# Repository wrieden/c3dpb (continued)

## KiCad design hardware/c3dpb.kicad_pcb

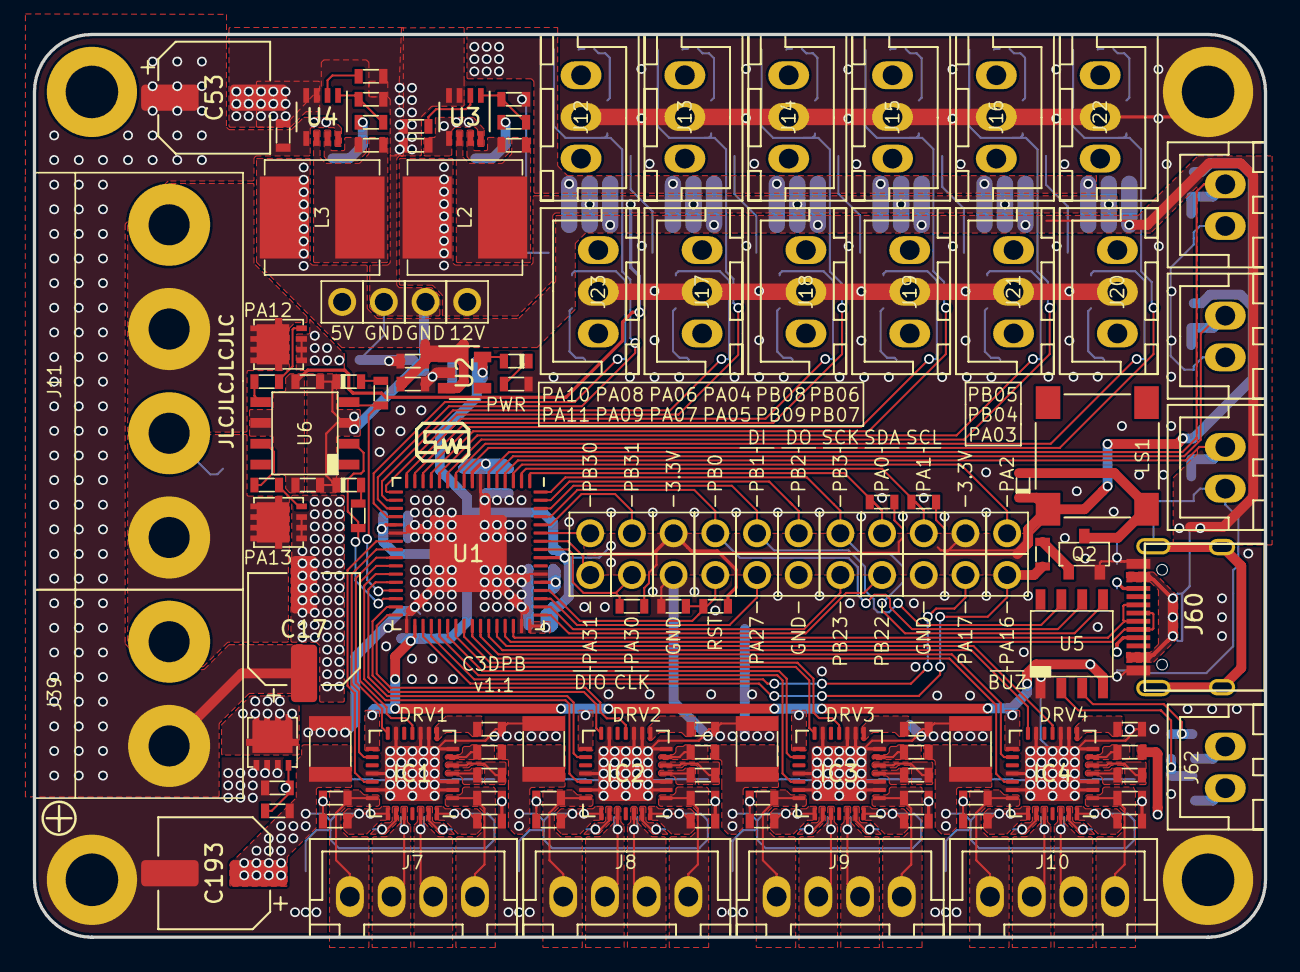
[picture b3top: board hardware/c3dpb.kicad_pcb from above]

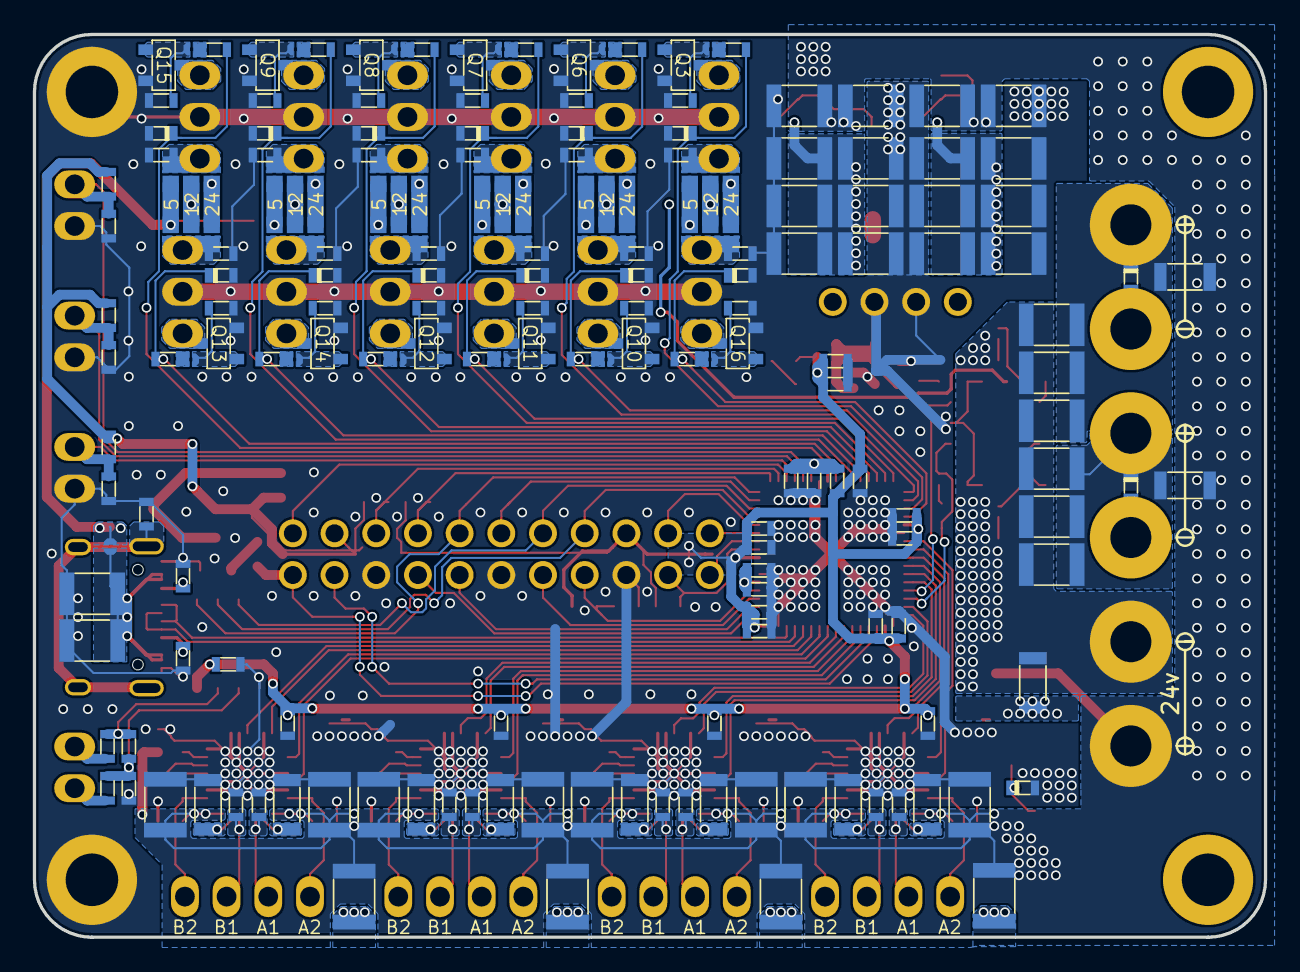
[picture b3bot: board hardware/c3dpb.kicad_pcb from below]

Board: 2 copper layers, 75.0 x 55.0 mm, 325 parts (189 on the bottom side), 179 nets.

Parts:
C1, C3, C5, C6, C8, C10, C11, C12, C16, C26, C45, C46, C50, C54, C58, C66, C79, C83, C86, C94, C97, C105, C108, C116, C117, C118, C119: 100n; 0603_CAP
C2, C4, C7, C9, C13, C14, C15, C18, C19, C20, C21, C22, C49, C59, C60, C61, C85, C96, C107: 10u; 0603_CAP
C17, C53, C193: 220u; CP_Elec_6.3x7.7
C23, C24, C25, C27, C47, C52, C55, C56, C57, C62, C63, C65, C84, C88, C95, C99, C106, C110, C120, C121, C122, C123, C124, C125, C126, C127: 4.7u; 1210_CAP
C28, C37: 10n; 0603_CAP
C30, C31, C32, C33, C34, C35, C36, C38, C40, C41, C42, C43, C44, C89: 22u; 1210_CAP
C48, C51, C87, C98, C109: 22n; 0603_CAP
C64, C67, C68, C69, C70, C71, C72, C73, C74, C75, C76, C77: 1u; 0603_CAP
C78, C80, C81, C82, C90, C91, C92, C93, C101, C102, C103, C104, C112, C113, C114, C115: 470p; 0603_CAP
D1: 16v; SOD-523_DIODE
D2, D18, D19: MSK4010; SOD-523_DIODE
D3, D4, D5: LED; 0603_LED
D6, D7, D8, D9, D10, D11, D12, D13, D14, D15, D16, D17: 3.6v; SOD-523_DIODE
F1, F2, F3: Fuse; 1206_RES
FB1, FB2, FB3, FB4: 470r/100mhz; 0603_IND
H1, H2, H3, H4: M3; MountingHole_3.2mm_M3_ISO14580_Pad
IC1, IC2, IC3, IC4: TMC2209; QFN-28-1EP_5x5mm_P0.5mm_EP3.35x3.35mm
J1, J2, J3, J4, J5, J6, J24, J25, J26, J27, J28, J29, J30, J31, J32, J33, J34, J45, J48, J49, J56, J57, J58, J59, J94, J95: Conn_01x01; PinHeader_2.54mm_1P
J7, J8, J9, J10: Conn_01x04; JST_XH_4P
J11: Screw_Terminal_01x04; KF635-4P
J12, J13, J14, J15, J16, J17, J18, J19, J20, J21, J22, J23: Conn_01x03; JST_XH_3P
J39: Screw_Terminal_01x02; KF635-2P
J60: USB_C_Receptacle; TYPE-C-31-M-12
J62, J71, J72, J73: Conn_01x02; JST_XH_2P
JP2, JP3, JP5, JP6, JP8, JP9, JP11, JP12, JP14, JP15, JP17, JP19, JP20, JP22, JP23, JP25, JP26, JP28, JP29, JP31, JP32, JP34, JP35, JP37, JP38: SolderJumper_2_Open; Solder Jumper 2P
JP4, JP7, JP10, JP13, JP18, JP21, JP24, JP27, JP30, JP33, JP36, JP39: SolderJumper_4_Open; SolderJumper_JST
L2, L3: BCIHP0750-6R8M; 7x7mm_IND
LS1: Buzzer; Buzzer-7525
Q1, Q4, Q5: AON7418; DFN3x3A_8L_EP1_P
Q2, Q3, Q6, Q7, Q8, Q9, Q10, Q11, Q12, Q13, Q14, Q15, Q16: AO3402; SOT-23
R1, R4, R5: 10k; 0603_RES
R2, R3: 10R; 0603_RES
R6, R18, R21, R22, R30, R32, R34, R36, R37, R39, R41, R42, R44, R46, R47, R48, R50, R51, R53, R55: 4.7k; 0603_RES
R7, R9, R31, R33, R35, R38, R40, R43, R45, R49, R52, R54, R56: 1meg; 0603_RES
R8, R11, R12, R15, R17: 100k; 0603_RES
R10, R14, R16: 1k; 0603_RES
R13: 13.3k; 0603_RES
R19, R20, R24, R25, R26, R27, R28, R29: 120m; 1206_RES
R23: 0R; 0603_RES
U1: ATSAMD51J19A-M; QFN-64-1EP_9x9mm_P0.5mm_EP4.7x4.7mm
U2: SE5218ALG-LF; SOT-23-5
U3, U4: SY8303; TSOT-23-8
U5: MAX6675; SO-8
U6: IR4427S; SO-8

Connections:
+3V3: C2.1, C4.1, C6.1, C7.1, C8.1, C9.1, C10.1, C11.1, C14.1, C21.1, C22.1, C45.1, C54.2, C58.2, C66.2, C79.2, D2.1, D4.2, FB2.2, IC1.15, IC2.15, IC3.15, IC4.15, J94.1, J95.1, LS1.1, R1.1, R10.1, R37.1, R42.1, R46.1, R48.1, R50.1, U1.21, U1.34, U1.48, U1.56, U2.5, U5.4
+5V: C18.1, C20.1, C33.1, C34.1, C38.1, C40.1, C43.1, C44.1, J48.1, JP4.2, JP7.2, JP10.2, JP13.2, JP15.2, JP18.2, JP21.4, JP24.4, JP27.4, JP30.4, JP33.4, JP36.2, JP39.4, L3.2, R12.1, U2.1, U2.3
+12V: C15.1, C16.1, C30.1, C32.1, C35.1, C36.1, C41.1, C42.1, J45.1, JP4.3, JP7.3, JP10.3, JP13.3, JP18.3, JP21.3, JP24.3, JP27.3, JP30.3, JP33.3, JP36.3, JP39.3, L2.2, R17.1, U6.6
+24V: C3.1, C5.1, C17.1, C23.1, C24.1, C25.1, C27.1, C46.2, C47.1, C50.2, C52.1, C53.1, C83.2, C84.1, C86.2, C88.1, C94.2, C95.1, C97.2, C99.1, C105.2, C106.1, C108.2, C110.1, C116.2, C117.2, C118.2, C119.2, C120.1, C121.1, C122.1, C123.1, C124.1, C125.1, C126.1, C127.1, C193.1, F2.2, F3.2, IC1.22, IC1.28, IC2.22, IC2.28, IC3.22, IC3.28, IC4.22, IC4.28, J39.2, JP4.4, JP7.4, JP10.4, JP13.4, JP18.4, JP21.2, JP24.2, JP27.2, JP30.2, JP33.2, JP36.4, JP39.2, R8.1, U3.5, U3.8, U4.5, U4.8
/BUZZER: J6.1, R16.2, U1.35
/DRV1_DIAG: IC1.11, U1.26
/DRV1_DIR: IC1.19, U1.23
/DRV1_STEP: IC1.16, U1.24
/DRV1_UART: IC1.14, U1.25
/DRV2_DIAG: IC2.11, U1.32
/DRV2_DIR: IC2.19, U1.27
/DRV2_STEP: IC2.16, U1.28
/DRV2_UART: IC2.14, U1.31
/DRV3_DIAG: IC3.11, U1.40
/DRV3_DIR: IC3.19, U1.37
/DRV3_STEP: IC3.16, U1.38
/DRV3_UART: IC3.14, U1.39
/DRV4_DIAG: IC4.11, U1.44
/DRV4_DIR: IC4.19, U1.41
/DRV4_STEP: IC4.16, U1.42
/DRV4_UART: IC4.14, U1.43
/I2C_SCL: J4.1, R37.2, U1.2
/I2C_SDA: J3.1, R42.2, U1.1
/IO1: D6.1, R6.1, U1.19
/IO2: D7.1, R30.1, U1.17
/IO3: D8.1, R32.1, U1.15
/IO4: D9.1, R34.1, U1.13
/IO5: D10.1, R36.1, U1.11
/IO6: D16.1, R53.1, U1.9
/IO7: D17.1, R55.1, U1.20
/IO8: D11.1, R39.1, U1.18
/IO9: D12.1, R41.1, U1.16
/IO10: D13.1, R44.1, U1.14
/IO11: D15.1, R51.1, U1.12
/IO12: D14.1, R47.1, U1.10
/POW1: R5.1, U1.30, U6.2
/POW2: R4.1, U1.29, U6.4
/RST: C1.1, J24.1, R1.2, U1.52
/SPI_CS: J27.1, U1.61, U5.6
/SPI_MISO: J28.1, U1.62, U5.7
/SPI_MOSI: J29.1, U1.63
/SPI_SCK: J30.1, U1.64, U5.5
/SWCLK: J1.1, R10.2, U1.57
/SWDIO: J2.1, U1.58
/TH1: C60.1, J72.1, R48.2, U1.6
/TH2: C61.1, J71.1, R50.2, U1.5
/TH3: C59.1, J73.1, R46.2, U1.4
/USB_D+: J60.A6, J60.B6, U1.46
/USB_D-: J60.A7, J60.B7, U1.45
/VDDANA: C19.1, C26.1, FB2.1, U1.8
/VDDCORE: C12.1, C13.1, U1.53
DCIN-: C17.2, C55.2, C56.2, C57.2, C62.2, C63.2, C65.2, F1.2, J39.1, Q4.1, Q5.1
GND: C1.2, C2.2, C3.2, C4.2, C5.2, C6.2, C7.2, C8.2, C9.2, C10.2, C11.2, C12.2, C13.2, C14.2, C15.2, C16.2, C18.2, C19.2, C20.2, C21.2, C22.2, C23.2, C24.2, C25.2, C26.2, C27.2, C30.2, C31.2, C32.2, C33.2, C34.2, C35.2, C36.2, C38.2, C40.2, C41.2, C42.2, C43.2, C44.2, C45.2, C46.1, C47.2, C49.2, C52.2, C53.2, C54.1, C58.1, C59.2, C60.2, C61.2, C64.2, C66.1, C67.2, C68.2, C69.2, C70.2, C71.2, C72.2, C73.2, C74.2, C75.2, C76.2, C77.2, C78.2, C79.1, C80.2, C81.2, C82.2, C83.1, C84.2, C85.2, C88.2, C89.2, C90.2, C91.2, C92.2, C93.2, C94.1, C95.2, C96.2, C99.2, C101.2, C102.2, C103.2, C104.2, C105.1, C106.2, C107.2, C110.2, C112.2, C113.2, C114.2, C115.2, C116.1, C117.1, C118.1, C119.1, C120.2, C121.2, C122.2, C123.2, C124.2, C125.2, C126.2, C127.2, C193.2, D1.2, D3.1, D5.1, D6.2, D7.2, D8.2, D9.2, D10.2, D11.2, D12.2, D13.2, D14.2, D15.2, D16.2, D17.2, FB1.1, H2.1, H3.1, H4.1, IC1.2, IC1.3, IC1.7, IC1.9, IC1.10, IC1.13, IC1.18, IC1.20, IC1.29, IC2.2, IC2.3, IC2.7, IC2.9, IC2.10, IC2.13, IC2.18, IC2.20, IC2.29, IC3.2, IC3.3, IC3.7, IC3.9, IC3.10, IC3.13, IC3.18, IC3.20, IC3.29, IC4.2, IC4.3, IC4.7, IC4.9, IC4.10, IC4.13, IC4.18, IC4.20, IC4.29, J12.2, J13.2, J14.2, J15.2, J16.2, J17.2, J18.2, J19.2, J20.2, J21.2, J22.2, J23.2, J49.1, J56.1, J57.1, J58.1, J59.1, J60.A1, J60.A12, J60.B1, J60.B12, J71.2, J72.2, J73.2, Q1.1, Q2.2, Q3.2, Q6.2, Q7.2, Q8.2, Q9.2, Q10.2, Q11.2, Q12.2, Q13.2, Q14.2, Q15.2, Q16.2, R7.2, R9.2, R11.2, R13.2, R14.2, R15.2, R18.2, R19.2, R20.2, R21.2, R22.2, R23.1, R24.2, R25.2, R26.2, R27.2, R28.2, R29.2, R31.2, R33.2, R35.2, R38.2, R40.2, R43.2, R45.2, R49.2, R52.2, R54.2, R56.2, U1.7, U1.22, U1.33, U1.47, U1.54, U1.65, U2.2, U3.3, U3.4, U4.3, U4.4, U5.1, U6.3
unnamed: C28.1, U4.7
unnamed: C28.2, L3.1, U4.6
unnamed: C31.1, C89.1, J60.A4, J60.A9, J60.B4, J60.B9, JP15.1
unnamed: C37.1, U3.7
unnamed: C37.2, L2.1, U3.6
unnamed: C48.1, FB3.1, U5.3
unnamed: C48.2, FB4.1, R23.2, U5.2
unnamed: C49.1, IC1.8
unnamed: C50.1, IC1.6
unnamed: C51.1, IC1.5
unnamed: C51.2, IC1.4
unnamed: C55.1, C56.1, C57.1, D19.1, F3.1, J11.1
unnamed: C62.1, C63.1, C65.1, D18.1, F2.1, J11.3
unnamed: C64.1, J12.1, JP4.1
unnamed: C67.1, J13.1, JP7.1
unnamed: C68.1, J14.1, JP10.1
unnamed: C69.1, J15.1, JP13.1
unnamed: C70.1, J16.1, JP18.1
unnamed: C71.1, J17.1, JP21.1
unnamed: C72.1, J18.1, JP24.1
unnamed: C73.1, J19.1, JP27.1
unnamed: C74.1, J20.1, JP30.1
unnamed: C75.1, J21.1, JP33.1
unnamed: C76.1, J22.1, JP36.1
unnamed: C77.1, J23.1, JP39.1
unnamed: C78.1, IC1.24, J7.3
unnamed: C80.1, IC1.21, J7.4
unnamed: C81.1, IC1.26, J7.2
unnamed: C82.1, IC1.1, J7.1
unnamed: C85.1, IC2.8
unnamed: C86.1, IC2.6
unnamed: C87.1, IC2.5
unnamed: C87.2, IC2.4
unnamed: C90.1, IC2.24, J8.3
unnamed: C91.1, IC2.21, J8.4
unnamed: C92.1, IC2.26, J8.2
unnamed: C93.1, IC2.1, J8.1
unnamed: C96.1, IC3.8
unnamed: C97.1, IC3.6
unnamed: C98.1, IC3.5
unnamed: C98.2, IC3.4
unnamed: C101.1, IC3.24, J9.3
unnamed: C102.1, IC3.21, J9.4
unnamed: C103.1, IC3.26, J9.2
unnamed: C104.1, IC3.1, J9.1
unnamed: C107.1, IC4.8
unnamed: C108.1, IC4.6
unnamed: C109.1, IC4.5
unnamed: C109.2, IC4.4
unnamed: C112.1, IC4.24, J10.3
unnamed: C113.1, IC4.21, J10.4
unnamed: C114.1, IC4.26, J10.2
unnamed: C115.1, IC4.1, J10.1
unnamed: D1.1, Q1.2, R8.2, R9.1
unnamed: D2.2, LS1.2, Q2.3
unnamed: D3.2, R4.2
unnamed: D4.1, R14.1
unnamed: D5.2, R5.2
unnamed: D18.2, J11.4, Q4.3
unnamed: D19.2, J11.2, Q5.3
unnamed: F1.1, Q1.3
unnamed: FB1.2, J60.S1
unnamed: FB3.2, J62.1
unnamed: FB4.2, J62.2
unnamed: IC1.23, R20.1
unnamed: IC1.27, R19.1
unnamed: IC2.23, R25.1
unnamed: IC2.27, R24.1
unnamed: IC3.23, R27.1
unnamed: IC3.27, R26.1
unnamed: IC4.23, R29.1
unnamed: IC4.27, R28.1
unnamed: J5.1, U1.3
unnamed: J12.3, JP3.1, Q3.3
unnamed: J13.3, JP6.1, Q6.3
unnamed: J14.3, JP9.1, Q7.3
unnamed: J15.3, JP12.1, Q8.3
unnamed: J16.3, JP17.1, Q9.3
unnamed: J17.3, JP20.1, Q10.3
unnamed: J18.3, JP23.1, Q11.3
unnamed: J19.3, JP26.1, Q12.3
unnamed: J20.3, JP29.1, Q13.3
unnamed: J21.3, JP32.1, Q14.3
unnamed: J22.3, JP35.1, Q15.3
unnamed: J23.3, JP38.1, Q16.3
unnamed: J25.1, U1.36
unnamed: J26.1, U1.51
unnamed: J31.1, U1.49
unnamed: J32.1, U1.50
unnamed: J33.1, U1.59
unnamed: J34.1, U1.60
unnamed: J60.A5, R22.1
unnamed: J60.B5, R21.1
unnamed: JP2.1, JP3.2, R6.2
unnamed: JP2.2, Q3.1, R7.1
unnamed: JP5.1, JP6.2, R30.2
unnamed: JP5.2, Q6.1, R31.1
unnamed: JP8.1, JP9.2, R32.2
unnamed: JP8.2, Q7.1, R33.1
unnamed: JP11.1, JP12.2, R34.2
unnamed: JP11.2, Q8.1, R35.1
unnamed: JP14.1, JP17.2, R36.2
unnamed: JP14.2, Q9.1, R38.1
unnamed: JP19.1, JP20.2, R39.2
unnamed: JP19.2, Q10.1, R40.1
unnamed: JP22.1, JP23.2, R41.2
unnamed: JP22.2, Q11.1, R43.1
unnamed: JP25.1, JP26.2, R44.2
unnamed: JP25.2, Q12.1, R45.1
unnamed: JP28.1, JP29.2, R47.2
unnamed: JP28.2, Q13.1, R49.1
unnamed: JP31.1, JP32.2, R51.2
unnamed: JP31.2, Q14.1, R52.1
unnamed: JP34.1, JP35.2, R53.2
unnamed: JP34.2, Q15.1, R54.1
unnamed: JP37.1, JP38.2, R55.2
unnamed: JP37.2, Q16.1, R56.1
unnamed: Q2.1, R16.1
unnamed: Q4.2, R2.1
unnamed: Q5.2, R3.1
unnamed: R2.2, U6.7
unnamed: R3.2, U6.5
unnamed: R11.1, U4.2
unnamed: R12.2, R13.1, U4.1
unnamed: R15.1, U3.2
unnamed: R17.2, R18.1, U3.1

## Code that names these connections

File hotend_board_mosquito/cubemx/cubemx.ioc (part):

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Mcu.Name=STM32G431K(6-8-B)Ux
Mcu.Package=UFQFPN32
Mcu.UserName=STM32G431KBUx
PA0.Mode=INP
PA0.Signal=COMP3_INP
PA1.Mode=PGA_Internally_Connected
PA1.Signal=OPAMP1_VINP
PA10.Signal=S_TIM1_CH3
PA11.Mode=Device
PA11.Signal=USB_DM
PA12.Mode=Device
PA12.Signal=USB_DP
PA13.Mode=Serial_Wire
PA13.Signal=SYS_JTMS-SWDIO
PA14.Mode=Serial_Wire
PA14.Signal=SYS_JTCK-SWCLK
PA15.Mode=NSS_Signal_Hard_Output
PA15.Signal=SPI1_NSS
PA2.Signal=ADC1_IN3
PA3.Mode=PGA_Internally_Connected
PA3.Signal=OPAMP1_VINM0
PA4.Signal=COMP_DAC11_group
PA5.Mode=PGA_Internally_Connected
PA5.Signal=OPAMP2_VINM0
PA6.Signal=ADC2_IN3
PA7.Mode=PGA_Internally_Connected
PA7.Signal=OPAMP2_VINP
PA8.Signal=S_TIM1_CH1
PA9.Signal=S_TIM1_CH2
PB0.Mode=INP
PB0.Signal=COMP4_INP
PB3.Mode=Full_Duplex_Master
PB3.Signal=SPI1_SCK
PB4.Mode=Full_Duplex_Master
PB4.Signal=SPI1_MISO
PB5.Mode=Full_Duplex_Master
PB5.Signal=SPI1_MOSI
PB6.GPIOParameters=GPIO_Label
PB6.GPIO_Label=buck2_switch
PB6.Signal=S_TIM4_CH1
PB7.GPIOParameters=GPIO_Label
PB7.GPIO_Label=buck1_switch
PB7.Signal=S_TIM3_CH4
PB8-BOOT0.GPIOParameters=GPIO_Label
PB8-BOOT0.GPIO_Label=hearter_switch
PB8-BOOT0.Signal=S_TIM8_CH2
RCC.HSE_VALUE=8000000
RCC.SYSCLKFreq_VALUE=16000000
board=custom

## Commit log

2019-06-15 initial, replaced dc dc
2019-06-16 replaced stepper driver
2019-06-30 layout
2019-06-30 power reg
2019-07-19 combine
2019-07-20 new con
2019-07-20 replicate
2019-07-26 routing
2019-08-10 pcb v1
2020-02-15 pcb version 1.1
2020-03-15 bootloader
2020-03-15 corrected openocd command
2020-03-16 remove klipper submodule
2020-03-16 added klipper submodule
2020-03-16 added config
2020-03-29 hotend board
2020-03-29 hotend board v1.0
2020-03-29 value fixes
2020-09-08 added libs as subrepos
2023-03-31 idk backup...
